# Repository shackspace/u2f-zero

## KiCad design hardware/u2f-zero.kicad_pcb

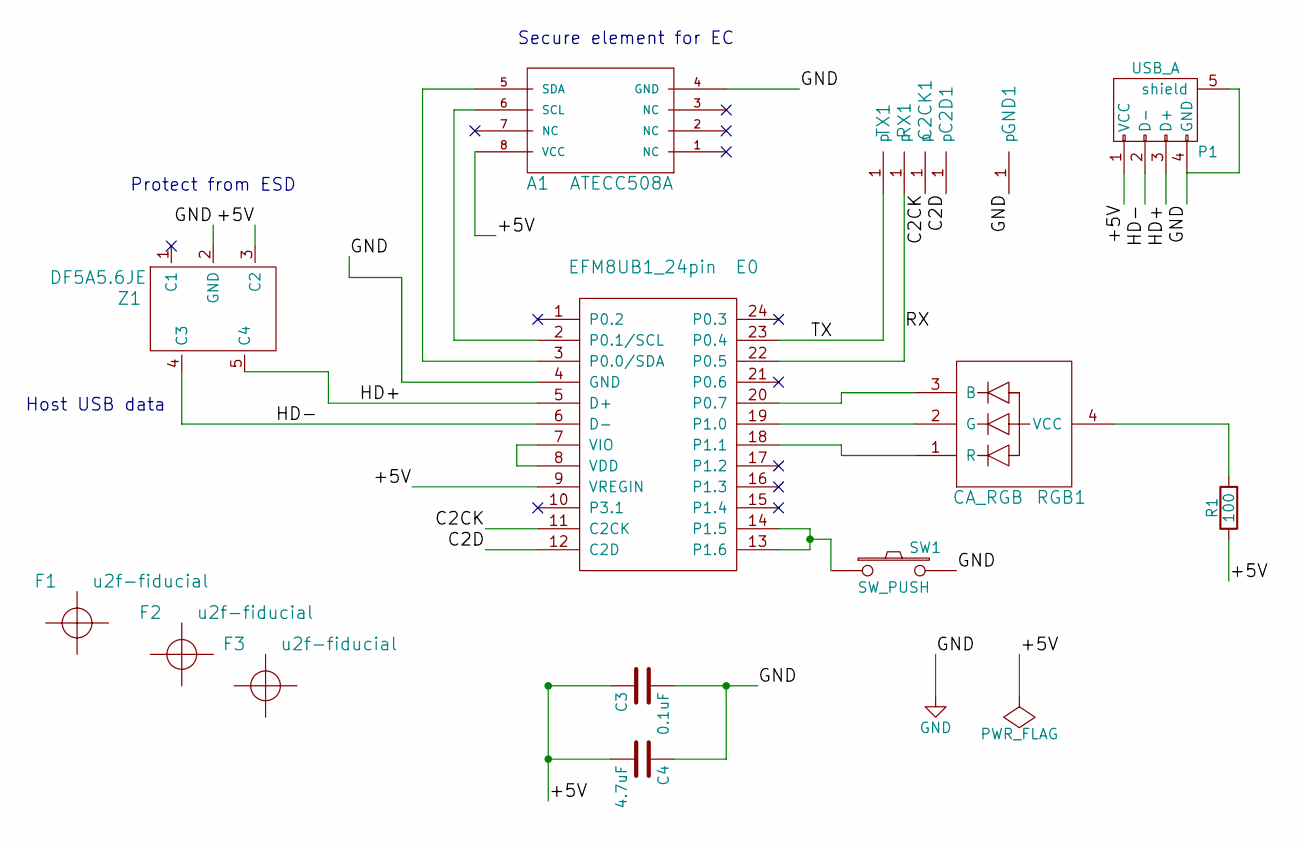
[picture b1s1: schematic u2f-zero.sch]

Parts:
A1: ATECC508A; SOIC-8_3.9x4.9mm_Pitch1.27mm; MFG Part Num ATECC508A-SSHDA-B
C2CK1, C2D1: debug-pin; debug
C3: 0.1uF; C_0402; MFG Part Num CL05A104MP5NNNC
C4: 4.7uF; C_0603; MFG Part Num CL10B475KQ8NQNC
E0: EFM8UB1_24pin; QSOP-24_3.9x8.7mm_Pitch0.635mm_fat; MFG Part Num EFM8UB11F16G-C-QSOP24
F1, F2, F3: u2f-fiducial
GND1: debug-pin; debug
P1: USB_A; USB_A_CON
R1: 100; R_0603; MFG Part Num CRCW0603100RFKEA
RGB1: CA_RGB; LED-0606; MFG Part Num LTST-C19HE1WT
RX1: debug-pin; debug
SW1: SW_PUSH; u2f-button; MFG Part Num TL3305AF260QG
TX1: debug-pin; debug
Z1: DF5A5.6JE; SOT-553; MFG Part Num DF5A5.6JE,LM

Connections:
/+5V: A1.8 (VCC), C3.1, C4.2, E0.9 (VREGIN), P1.1 (VCC), R1.1, Z1.3 (C2)
/C2CK: C2CK1.1, E0.11 (C2CK)
/C2D: C2D1.1, E0.12 (C2D)
/HD+: E0.5 (D+), P1.3 (D+), Z1.5 (C4)
/HD-: E0.6 (D-), P1.2 (D-), Z1.4 (C3)
/RX: E0.22 (P0.5), RX1.1
/TX: E0.23 (P0.4), TX1.1
GND: A1.4 (GND), C3.2, C4.1, E0.4 (GND), GND1.1, P1.4 (GND), P1.5 (shield), SW1.2, Z1.2 (GND)
unnamed: A1.5 (SDA), E0.3 (P0.0/SDA)
unnamed: A1.6 (SCL), E0.2 (P0.1/SCL)
unnamed: E0.7 (VIO), E0.8 (VDD)
unnamed: E0.13 (P1.6), E0.14 (P1.5), SW1.1
unnamed: E0.18 (P1.1), RGB1.1 (R)
unnamed: E0.19 (P1.0), RGB1.2 (G)
unnamed: E0.20 (P0.7), RGB1.3 (B)
unnamed: R1.2, RGB1.4 (VCC)

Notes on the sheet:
Protect from ESD
Host USB data
Secure element for EC

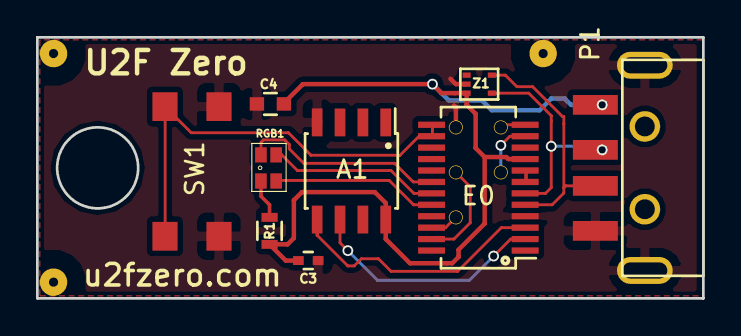
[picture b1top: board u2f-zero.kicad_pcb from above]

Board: 2 copper layers, 37.0 x 14.5 mm, 17 parts (0 on the bottom side), 16 nets.

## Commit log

2016-10-03 changed usb connector from pcb connector to surface soldered connector
2016-10-22 first attempt at creating a 3d printable (sla/sls) clippable case
    next: test print, modify, order?!
2017-02-07 changed push button hole position
2017-03-23 case complete (USB plug version)
    Testprints, minor changes made. Done.
